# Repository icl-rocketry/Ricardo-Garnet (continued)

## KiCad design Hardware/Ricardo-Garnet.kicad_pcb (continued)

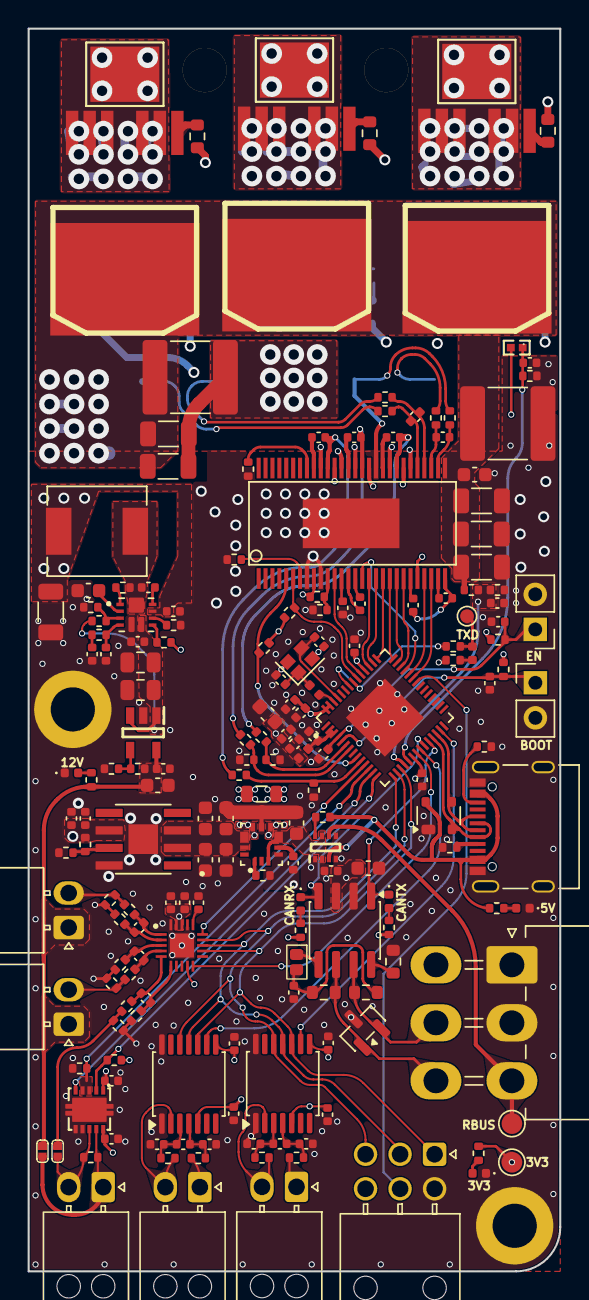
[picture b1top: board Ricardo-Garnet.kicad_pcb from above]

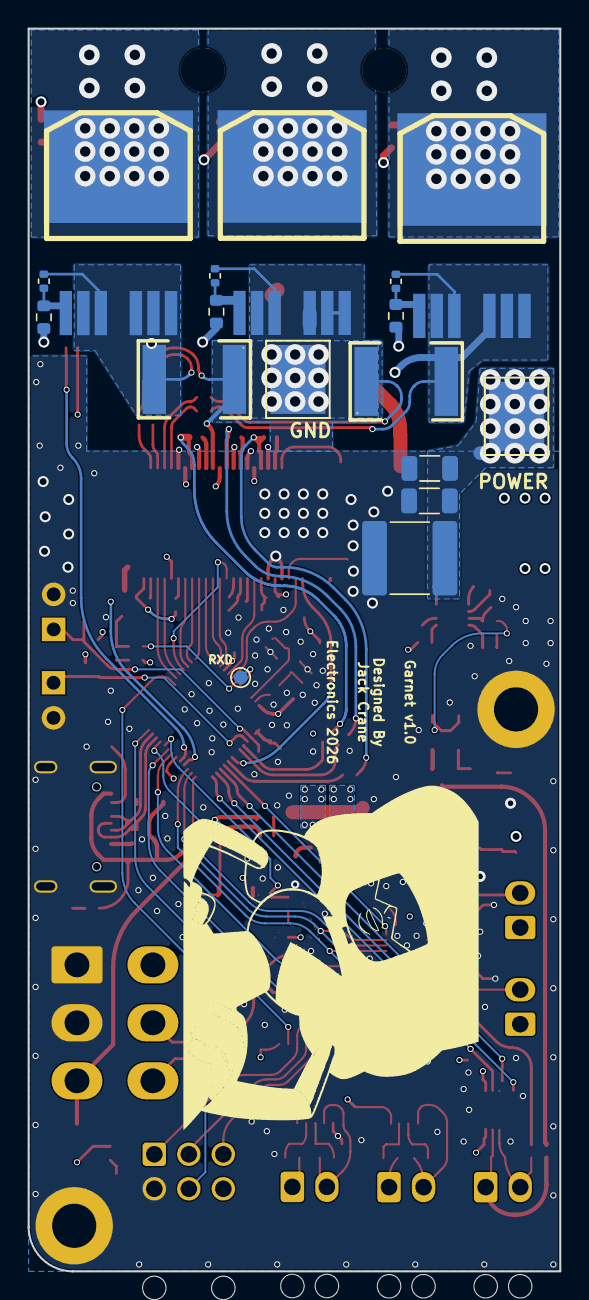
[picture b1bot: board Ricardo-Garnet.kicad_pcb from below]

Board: 4 copper layers, 38.5 x 90.0 mm, 205 parts (17 on the bottom side), 132 nets.

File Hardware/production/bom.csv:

Designator,Footprint,Quantity,Value,LCSC Part #
12VLED101,0402,1,RED_LED,
3V3LED101,0402,1,BLUE_LED,
"C101, C202, C301, C303, C304, C305, C306",0603,7,10uF,
"C102, C103, C107, C302, C513, C514, C602, C606",0402,8,1uF,
"C104, C105, C106, C109, C110, C111, C114, C201, C308, C404, C405, C407, C411, C501, C503, C506, C508, C509, C510, C511, C512",0402,21,100nF,
"C108, C502, C504, C505, C507, C516, C517, C518",0402,8,10nF,
"C112, C113",0402,2,11pF,
"C115, C601",0402,2,2.2uF,
C203,0402,1,47nF,
C307,0402,1,10uF,
C401,0603,1,4.7uF,
C402,0402,1,75pF,
C403,0402,1,1.8nF,
C406,1206,1,47uF,
"C408, C409",0805,2,10uF,
C410,0603,1,1uF,
C515,0402,1,220nF,
"C603, C604, C608, C609, C612, C616, C617",1206,7,"10uF, 50V",
"C605, C610, C618",2220,3,"15uF, 100V",
C607,0402,1,"22nF, 50V",
C611,0603,1,"100nF, 50V",
"C613, C614, C615",0402,3,"220nF, 50V",
"C701, C702",0402,2,2.2nF,
CANRXLED101,0402,1,ORANGE_LED,
"CANTXLED101, TXLED101",0402,2,GREEN_LED,
D201,SOT-23,1,SM712,
D801,SOT-143,1,SP0503BAHT,
"H101, H102, H103, H104",MountingHole_3.2mm_M3_DIN965_Pad,4,MountingHole_Pad,
IC401,IC_TPS61089RNRR,1,TPS61089RNRR,TPS61089RNRR
IC402,SOT95P282X145-5N,1,AP2205-W5-7,AP2205-W5-7
IC501,QFN40P300X300X80-21N-D,1,ADS131M04IRUKR,ADS131M04IRUKR
J101,Molex_Mini-Fit_Jr_5569-06A2_2x03_P4.20mm_Horizontal,1,RBUS,
"J501, J502, J503, J504, J505",Molex_Nano-Fit_105313-xx02_1x02_P2.50mm_Horizontal,5,Conn_01x02_Male,
J506,Molex_Nano-Fit_105314-xx06_2x03_P2.50mm_Horizontal,1,3x2 Nanofit,
J801,USB_C_Receptacle_Palconn_UTC16-G,1,USB_C_Receptacle_USB2.0,
"JP101, JP102",PinHeader_1x02_P2.54mm_Vertical,2,Conn_01x02_Male,
JP201,SmallerSolderJP,1,TermJP,
L101,0402,1,2nH,
L102,0402,1,20nH,
L301,0805,1,1uH,
L401,IND_SRP6540-390M,1,SRR6038-3R3Y,
LED801,0402,1,WHITE_LED,
P101,1PAD_4x5mm,1,IN+,
P102,1PAD_4x5mm,1,IN-,
P701,1PAD_4x5mm,1,MOTOR3,
P702,1PAD_4x5mm,1,MOTOR2,
P703,1PAD_4x5mm,1,MOTOR1,
"Q701, Q702, Q703, Q704, Q705, Q706",D2PAK-7-GDS,6,IRFS7530,
"R101, R106, R112, R301, R304, R404, R501, R502, R603, R604, R605",0402,11,10kΩ,
"R102, R103, R104, R105, R510, R511, R512, R513, R515, R516",0402,10,1kΩ,
R107,0402,1,499Ω,
R108,0402,1,3kΩ,
"R109, R607, R609, R611, R703, R709, R712",0402,7,39kΩ,
"R110, R608, R610, R612",0402,4,2.2kΩ,
R111,R0402,1,NCU15XH103F6SRC,C333993
R201,0603,1,0Ω,
"R202, R203",0603,2,60Ω,
R302,0402,1,14kΩ,
R303,0402,1,56kΩ,
R401,0402,1,28.7kΩ,
R402,0402,1,866kΩ,
R403,0402,1,92kΩ,
R405,0402,1,332kΩ,
R406,0402,1,280kΩ,
R407,0402,1,49.9kΩ,
R408,0402,1,432kΩ,
"R503, R504, R505, R506, R704, R705, R713, R714",0402,8,100Ω,
R507,0402,1,120Ω,
"R508, R509, R514",0402,3,59Ω,RT0402BRD0749R9L
"R601, R602",0402,2,~,
R606,0402,1,1MΩ,
"R701, R702, R707, R708, R710, R711",0603,6,4.7Ω,
"R706, R715",RES-SMD_L7.1-W4.6_HOXLR2818,2,10mΩ,C53115042
"R801, R802, R803",0402,3,5.1kΩ,
"TP101, TP102",TestPoint_Pad_D1.0mm,2,TestPoint,
"TP301, TP302",TestPoint_Pad_D1.5mm,2,TestPoint,
U101,QFN40P700X700X90-57N,1,ESP32-S3,
U201,SOIC-8_3.9x4.9mm_P1.27mm,1,SN65HVD230,
U301,SOTFL50P160X60-8N,1,LM66200DRLR,
U302,CONV_MAX77827AEFD+T,1,MAX77827AEFD+T,
U303,SOIC127P599X175-9N,1,SC4215,
U501,VSON-10_L3.0-W3.0-P0.50-BL-EP_DRC,1,THVD2429DRCR,C41755914
"U502, U503",TSSOP-14_4.4x5mm_P0.65mm,2,MAX31856,
U601,TSSOP-56-PP,1,DRV8302,
Y101,Crystal_SMD_2016-4Pin_2.0x1.6mm,1,R940000171,

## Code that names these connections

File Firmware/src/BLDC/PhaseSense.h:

#pragma once
/*
 * Phase voltage sense via the 39k / 2k2 dividers on each motor phase.
 *
 * From the Ricardo-Garnet schematic (note the numbering is reversed):
 *   SENS1 (GPIO1) -> SH_C (phase C)
 *   SENS2 (GPIO2) -> SH_B (phase B)
 *   SENS3 (GPIO5) -> SH_A (phase A)
 *   AN_IN (GPIO13, ADC2) -> V_SUPPLY, same divider
 *
 * Divider ratio (39k + 2k2) / 2k2 = 18.73, so ~3.1 V ADC full scale ~= 58 V.
 */

#include "DRV8302.h"

class PhaseSense
{
public:
    static constexpr float R_TOP = 39000.0f;
    static constexpr float R_BOTTOM = 2200.0f;
    static constexpr float DIVIDER_RATIO = (R_TOP + R_BOTTOM) / R_BOTTOM;

    PhaseSense(int senseA, int senseB, int senseC, int senseSupply);

    void setup();

    // volts at the phase node / supply, after undoing the divider
    float readPhase(DRV8302::Phase phase) const;
    float readSupply() const;

private:
    const int _phasePin[3];
    const int _supplyPin;

    static float readDivided(int pin);
};

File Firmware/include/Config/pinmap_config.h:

/*
**********************
* PINS               *
**********************
* Ricardo-Garnet BLDC controller (ESP32-S3, QFN56, U101)
* Traced from Ricardo-Garnet.kicad_sch netlist (rev after commit 4d7588f)
 */
#pragma once

namespace PinMap{

    // --- Gate driver (Mosfet driver sheet, DRV8302 U601, 6-PWM mode) ---
    static constexpr int EnGate = 34;
    static constexpr int H1 = 40;
    static constexpr int L1 = 39;
    static constexpr int H2 = 38;
    static constexpr int L2 = 37;
    static constexpr int H3 = 36;
    static constexpr int L3 = 35;
    static constexpr int DcCal = 41;
    static constexpr int Fault = 42;     // open drain, pull-up R603
    static constexpr int OcTw = 4;       // overcurrent / overtemp warning, open drain, pull-up R605

    // --- Current shunt amps (DRV8302 SO1/SO2) ---
    // NOTE: GPIO33 and GPIO47 have no ADC on the ESP32-S3, so these
    // cannot be sampled as analog inputs on this board revision.
    static constexpr int BrSo1 = 33;
    static constexpr int BrSo2 = 47;

    // --- Phase voltage sense (ADC1) ---
    static constexpr int Sens1 = 1;      // ADC1_CH0 -> SH_C
    static constexpr int Sens2 = 2;      // ADC1_CH1 -> SH_B
    static constexpr int Sens3 = 5;      // ADC1_CH4 -> SH_A

    // --- Misc analog (ADC2 - unusable while WiFi is active) ---
    static constexpr int AnIn = 13;      // V_SUPPLY divider (39k / 2k2)
    static constexpr int MosTemp = 14;   // NTC 10k

    // --- SPI bus (sensors sheet) ---
    static constexpr int H_MISO = 10;
    static constexpr int H_MOSI = 11;
    static constexpr int H_SCLK = 12;

    // --- SPI chip selects ---
    static constexpr int AdcCs = 15;     // net "ACD_CS"
    static constexpr int TcCs_0 = 16;
    static constexpr int TcCs_1 = 21;
    static constexpr int EncoderCs = 48; // J506

    static constexpr int AdcClk = 6;     // net "ACD_CLK"

    // --- Modbus / RS485 ---
    static constexpr int ModDir = 7;
    static constexpr int ModTx = 8;
    static constexpr int ModRx = 9;

    // --- CAN ---
    static constexpr int TxCan = 18;
    static constexpr int RxCan = 17;

    // --- UART0 (test points TP101/TP102, TX LED) ---
    static constexpr int TxD = 43;       // via R107 499R
    static constexpr int RxD = 44;

    // --- USB (native USB-Serial-JTAG) ---
    static constexpr int UsbDm = 19;
    static constexpr int UsbDp = 20;

    // --- Boot ---
    static constexpr int Boot = 0;

    // Unconnected: 3, 45, 46 (26-32 reserved for flash)
};

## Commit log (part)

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2026-01-19 initial commit for schematic review
2026-01-19 formatting
2026-01-20 removed voltage pt sensing capabilities
2026-01-27 chatting to fang
2026-01-28 commit pre-hackspace request
2026-01-29 updated settled pcb design
2026-02-05 close to 1st done
2026-02-11 final touches and adding encoder
2026-02-11 forgot to close file
2026-03-21 removed some decoupling caps from sims
2026-03-21 mounting holes looking rough
2026-03-21 lcks
2026-03-21 touching up and adding thermals for coating
2026-05-12 added 2wire sensor and silkscreen
2026-05-12 tidied up repo
2026-05-28 changes made post will's review
2026-06-08 fixed mosfet error
